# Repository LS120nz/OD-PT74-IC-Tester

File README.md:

# OD-PT74

Pico 74xx Logic IC Tester

OD-PT74 is the first bench instrument in the Otter Designs Test Equipment family.

## PCB Manufacturing

Production-ready PCBs are available from the PCBWay Shared Project.

➡️ https://www.pcbway.com/project/shareproject/OD_PT74_Logic_IC_Tester_728014b9.html

An open-source bench instrument for testing classic 74xx-series logic ICs.

*OD-PT74 Pico 74xx IC Tester installed in the production enclosure.*

---

## Overview

The OD-PT74 Pico 74xx IC Tester is a Raspberry Pi Pico 2 (RP2040) based instrument designed to test common 74xx logic ICs used in retro-computing, electronics repair, education, and hobby projects.

The Rev-C platform combines dedicated hardware, a graphical OLED user interface, and modular MicroPython firmware to provide fast, repeatable testing of common logic devices in a compact desktop instrument.

Current support focuses on standard 14-pin, 16-pin, and 20-pin DIP devices from the 74LS, 74HC, 74HCT and selected compatible logic families.

## 🚀 Quick Start

1. Download or clone this repository.
2. Install **Thonny** from https://thonny.org
3. Install **MicroPython** onto your Raspberry Pi Pico.
4. Copy the following files to the Pico:
   - `main.py`
   - `ssd1306.py`
5. Power up the tester.
6. Verify the POST completes successfully.
7. Start testing ICs!

For detailed installation instructions, see the **Documentation Index** or jump directly to one of the guides below.

---

## Documentation

| Section | Description |
|---------|-------------|
| [📖 Documentation Index](docs/README.md) | Browse all project documentation |
| [🚀 Getting Started](docs/guides/getting-started.md) | First-time setup |
| [🔧 Build Guide](docs/guides/build-guide.md) | Hardware assembly |
| [🔧 Front Panel Wiring Guide](docs/guides/Switch-Wiring-guide.md)
| [💾 Firmware Guide](docs/guides/firmware-guide.md) | Install and update the firmware |
| [▶️ Usage Guide](docs/guides/usage-guide.md) | Operating the tester |
| [🧩 Supported ICs](docs/guides/supported-ics.md) | Supported logic device library |
| [🛠 Troubleshooting Guide](docs/guides/troubleshooting-guide.md) | Diagnose common issues |

---

## Key Features

* Raspberry Pi Pico 2 (RP2040) based design
* Supports standard 14-, 16- and 20-pin DIP packages
* Compatible with common 74LS, 74HC and 74HCT logic families
* Automatic package detection
* Quick, Full and Soak test modes
* Power-On Self Test (POST)
* 128×64 OLED graphical interface
* Rotary encoder driven menu system
* USB serial diagnostics
* Open-source hardware and firmware

---

## Gallery

*Figure 1. Full functional test in progress.*

* 

*Figure 2. OLED displaying a successful PASS result.*

*Figure 3. OLED displaying a FAIL result.*

*Figure 4. USB serial diagnostic output in Thonny.*

## Hardware Summary

| Feature      | Specification                            |
| ------------ | ---------------------------------------- |
| MCU          | Raspberry Pi Pico 2 (RP2040)               |
| Display      | 128 × 64 SSD1306 OLED                    |
| DUT Packages | 14, 16 and 20-pin DIP                    |
| DUT Supply   | 3.3 V / OFF / 5 V                        |
| Interface    | Rotary encoder + push buttons            |
| Firmware     | MicroPython                              |
| License      | MIT (firmware), CERN-OHL-S v2 (hardware) |

---

## Current Release

Hardware PCB Revision: Rev-C
Firmware Version: v1.0.0

This is the first public release of the OD-PT74.

Earlier PCB revisions (Rev-A and Rev-B) were internal development prototypes and were never publicly released.

The project is now focused on:

* expanding the verified IC library
* firmware maintenance and refinement
* documentation improvements
* community contributions

Advanced diagnostic capabilities are planned for the separate Logic IC Diagnostic Analyzer project.

---

## Hardware

Designed for through-hole construction using readily available components with a few SMDs.

Rev-C introduces a production-quality hardware platform featuring:

* Raspberry Pi Pico 2 controller
* 20-pin ZIF socket
* 3.3 V / OFF / 5 V DUT power selection
* Package selection for 14-, 16- and 20-pin devices
* MCP23017 I/O expansion
* SSD1306 OLED display
* Rotary encoder navigation
* TEST and NEXT push buttons
* RGB status LED
* Audible buzzer
* Shared I²C bus architecture
* 5 V power indicator LED
* 3.3 V power indicator LED

GPIO protection is provided through series resistors and clamp diodes to improve robustness during normal operation.

---

## Firmware

The firmware uses a modular architecture that separates hardware drivers, IC definitions, and user interface logic for ease of maintenance and future expansion.

Implemented functionality includes:

* Power-On Self Test (POST)
* OLED diagnostics
* I²C bus diagnostics
* MCP23017 detection
* Package detection
* DUT voltage detection
* Menu-driven user interface
* Serial diagnostic output
* Quick Test mode
* Full Functional Test mode
* Soak testing (50, 500 and Continuous)

---

## Test Modes

| Mode       | Description                                  |
| ---------- | -------------------------------------------- |
| Quick      | Fast functional verification                 |
| Full       | Complete functional testing                  |
| Soak 50    | 50 consecutive test cycles                   |
| Soak 500   | 500 consecutive test cycles                  |
| Continuous | Unlimited endurance testing                  |
| POST       | Automatic hardware self-test during power-up |

During startup the tester automatically verifies:

* OLED communication
* MCP23017 communication
* I²C bus operation
* Package selection
* DUT voltage selection
* TEST button operation

Diagnostic information is displayed on both the OLED and the USB serial console.

---

## Getting Started

1. Assemble the hardware.
2. Install MicroPython on the Raspberry Pi Pico 2.
3. Copy the firmware to the Pico.
4. Power on the tester.
5. Allow the Power-On Self Test to complete.
6. Select the package size.
7. Insert the IC into the ZIF socket.
8. Press **TEST**.

---

## Project Evolution

| Revision | Description                                    |
| -------- | ---------------------------------------------- |
| Rev-C    | First public production release of the OD-PT74 |

Earlier prototype revisions were used during development and are documented in the project history.

---

## Repository Layout

```text
hardware/
firmware/
graphics/
images/
templates/

docs/
├── README.md
├── guides/
├── reference/
├── development/
├── archive/
└── images/

README.md
CHANGELOG.md
CONTRIBUTING.md
LICENSE
```

---

## Contributing

Contributions are welcome, particularly:

* verified IC definitions
* bug reports
* documentation improvements
* hardware testing
* firmware enhancements

When submitting a new IC definition, please include:

* source code
* pin mapping
* tested device family
* hardware validation results
* Quick, Full and Soak test results where applicable

---

## License

Hardware is licensed under the **CERN-OHL-S v2**.

Firmware and documentation are licensed under the **MIT License**.

See the LICENSE file for details.

---

## Acknowledgements

Developed by **Otter Designs**, New Zealand.

If you build an OD-PT74, we'd love to see it! Share your photos, improvements, verified IC definitions, or project ideas by opening an issue or discussion on GitHub.

---

## Project Reference

| Document | Description |
|----------|-------------|
| [📐 Project Overview](docs/reference/project-overview.md) | Project goals and architecture |
| [📘 Hardware Design Guide](docs/reference/hardware-design-guide.md) | Hardware architecture and design |
| [📝 Documentation Style Guide](docs/reference/documentation-style-guide.md) | Documentation standards |

## Development

| Document | Description |
|----------|-------------|
| [📅 Milestones](docs/development/Milestones.md) | Project progress and milestones |

## Project Preservation

Where practical, the OD-PT74 repository includes the original source files used to create the project.

Examples include:

- KiCad PCB source
- FreeCAD enclosure source
- SVG diagrams
- Firmware source code
- Documentation source

This approach helps ensure the project remains buildable, maintainable and adaptable for many years to come.

| [✅ Bring-up Checklist](docs/development/bringup-checklist.md) | Hardware verification checklist |

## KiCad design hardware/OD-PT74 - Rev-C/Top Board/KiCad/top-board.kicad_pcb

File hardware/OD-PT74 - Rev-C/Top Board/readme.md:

# OD-PT74 Rev-C Top Board

This directory contains all design, manufacturing and reference files for the **OD-PT74 Rev-C Top Board**.

## Contents

### BOM

Contains the Bill of Materials in both human-readable Markdown and KiCad-generated CSV formats.

### KiCad

Contains the complete KiCad source project, including the schematic, PCB layout and associated project files.

### Gerbers

Contains the Gerber and drill files generated from the final Rev-C design.

### Images

Contains reference images, including the schematic, PCB layout and 3D board render.

### OD-PT74_Top.zip

A ready-to-upload archive containing all manufacturing files required for PCB fabrication.

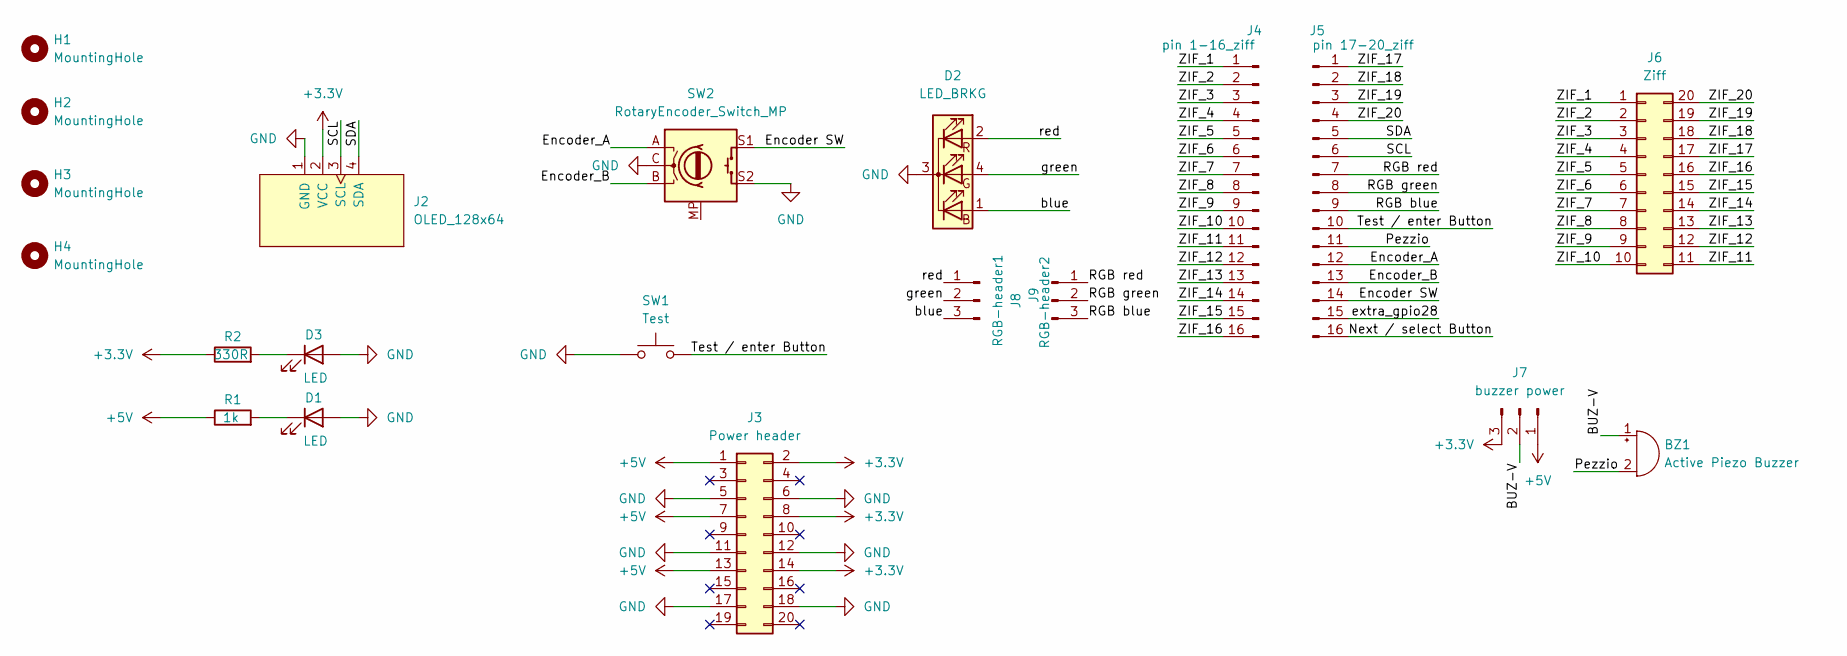
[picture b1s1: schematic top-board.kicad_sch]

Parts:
BZ1: Active Piezo Buzzer; Buzzer_15x7.5RM7.6
D1, D3: LED; LED_D3.0mm
D2: LED_BRKG; LED_D5.0mm-4_RGB_Staggered_Pins
H1, H2, H3, H4: MountingHole; MountingHole_3.2mm_M3
J2: OLED_128x64
J3: Power header; PinHeader_2x10_P2.54mm_Vertical
J4: pin 1-16_ziff; PinHeader_1x16_P2.54mm_Vertical
J5: pin 17-20_ziff; PinHeader_1x16_P2.54mm_Vertical
J6: Ziff; DIP_Socket-20_W4.3mm_W5.08mm_W7.62mm_W10.16mm_W10.9mm_3M_22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
J7: buzzer power; PinHeader_1x03_P2.54mm_Horizontal
J8: RGB-header1; PinHeader_1x03_P2.54mm_Vertical
J9: RGB-header2; PinHeader_1x03_P2.54mm_Vertical
R1: 1k; R_Axial_DIN0207_L6.3mm_D2.5mm_P7.62mm_Horizontal
R2: 330R; R_Axial_DIN0207_L6.3mm_D2.5mm_P7.62mm_Horizontal
SW1: Test; SW_PUSH_6mm
SW2: RotaryEncoder_Switch_MP; RotaryEncoder_Alps_EC11E-Switch_Vertical_H20mm

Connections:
+3.3V: J2.2 (VCC), J3.2, J3.8, J3.14, J7.3, R2.1
+5V: J3.1, J3.7, J3.13, J7.1, R1.1
/BUZ-V: BZ1.1 (+), J7.2
/Encoder SW: J5.14, SW2.S1
/Encoder_A: J5.12, SW2.A
/Encoder_B: J5.13, SW2.B
/Next / select Button: J5.16
/Pezzio: BZ1.2 (-), J5.11
/RGB blue: J5.9, J9.3
/RGB green: J5.8, J9.2
/RGB red: J5.7, J9.1
/SCL: J2.3 (SCL), J5.6
/SDA: J2.4 (SDA), J5.5
/Test / enter Button: J5.10, SW1.2
/ZIF_1: J4.1, J6.1
/ZIF_2: J4.2, J6.2
/ZIF_3: J4.3, J6.3
/ZIF_4: J4.4, J6.4
/ZIF_5: J4.5, J6.5
/ZIF_6: J4.6, J6.6
/ZIF_7: J4.7, J6.7
/ZIF_8: J4.8, J6.8
/ZIF_9: J4.9, J6.9
/ZIF_10: J4.10, J6.10
/ZIF_11: J4.11, J6.11
/ZIF_12: J4.12, J6.12
/ZIF_13: J4.13, J6.13
/ZIF_14: J4.14, J6.14
/ZIF_15: J4.15, J6.15
/ZIF_16: J4.16, J6.16
/ZIF_17: J5.1, J6.17
/ZIF_18: J5.2, J6.18
/ZIF_19: J5.3, J6.19
/ZIF_20: J5.4, J6.20
/blue: D2.1 (BA), J8.3
/extra_gpio28: J5.15
/green: D2.4 (GA), J8.2
/red: D2.2 (RA), J8.1
GND: D1.2 (A), D2.3 (K), D3.2 (A), J2.1 (GND), J3.5, J3.6, J3.11, J3.12, J3.17, J3.18, SW1.1, SW2.C, SW2.S2
unnamed: D1.1 (K), R1.2
unnamed: D3.1 (K), R2.2

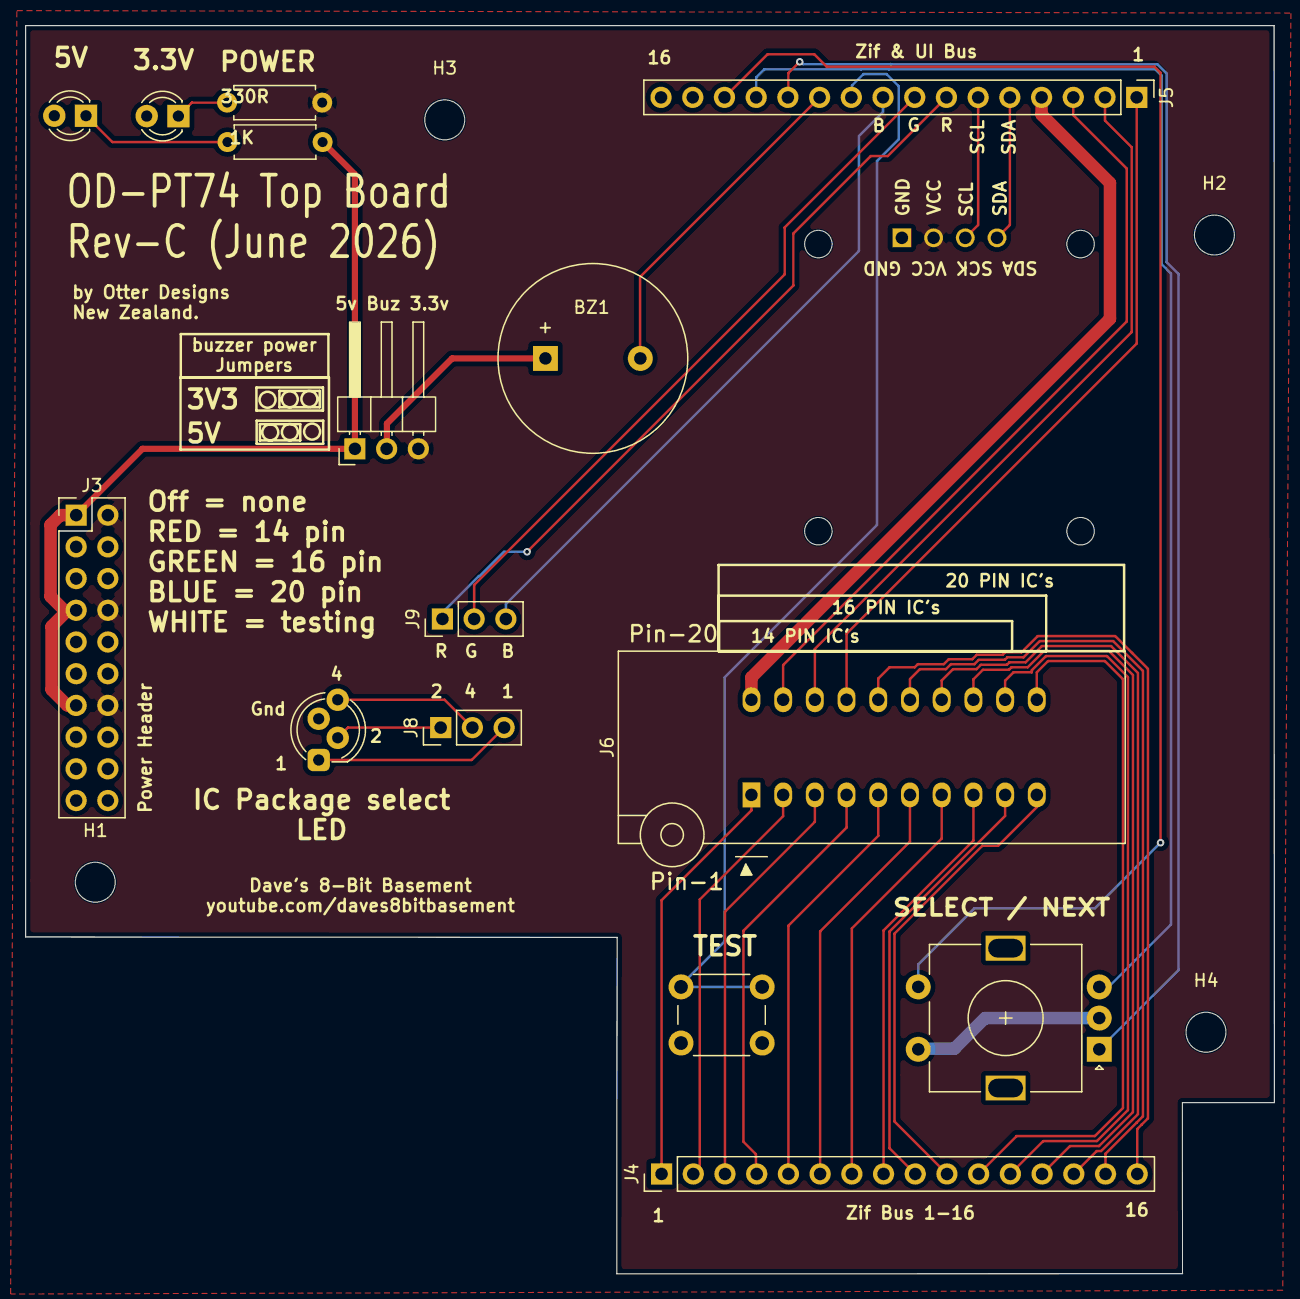
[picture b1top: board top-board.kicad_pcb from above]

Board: 2 copper layers, 100.0 x 100.0 mm, 20 parts (0 on the bottom side), 39 nets.

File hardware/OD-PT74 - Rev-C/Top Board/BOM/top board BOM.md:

# OD-PT74 Rev-C Top Board

*Bill of Materials*
-------------------------

1 × Active Piezo Buzzer (BZ1)

2 × 3 mm Power LEDs (D1, D3)
    - Red
    - Green

1 × RGB LED (D2)

1 × Power Switch, ON/OFF/ON (J1)

1 × 128×64 OLED Display Header (J2)

1 × 2×10 Board Connector (J3)

2 × 1×16 Headers (J4, J5)

1 × 20-pin ZIF Socket

1 × 1 kΩ Resistor (R1)

1 × 330 Ω Resistor (R2)

1 × 6×6 mm Tactile Push Button (SW1)

1 × EC11E Vertical Low-Profile Rotary Encoder (SW2)

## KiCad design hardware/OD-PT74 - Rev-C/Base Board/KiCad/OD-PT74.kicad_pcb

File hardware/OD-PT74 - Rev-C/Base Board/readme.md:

# OD-PT74 Rev-C Base Board

This directory contains all design, manufacturing and reference files for the **OD-PT74 Rev-C Base Board**.

## Contents

### BOM

Contains the Bill of Materials in both human-readable Markdown and KiCad-generated CSV formats.

### KiCad

Contains the complete KiCad source project, including the schematic, PCB layout and associated project files.

### Gerbers

Contains the Gerber and drill files generated from the final Rev-C design.

### Images

Contains reference images, including the schematic, PCB layout and 3D board render.

### OD-PT74_Base.zip
A ready-to-upload archive containing all manufacturing files required for PCB fabrication.

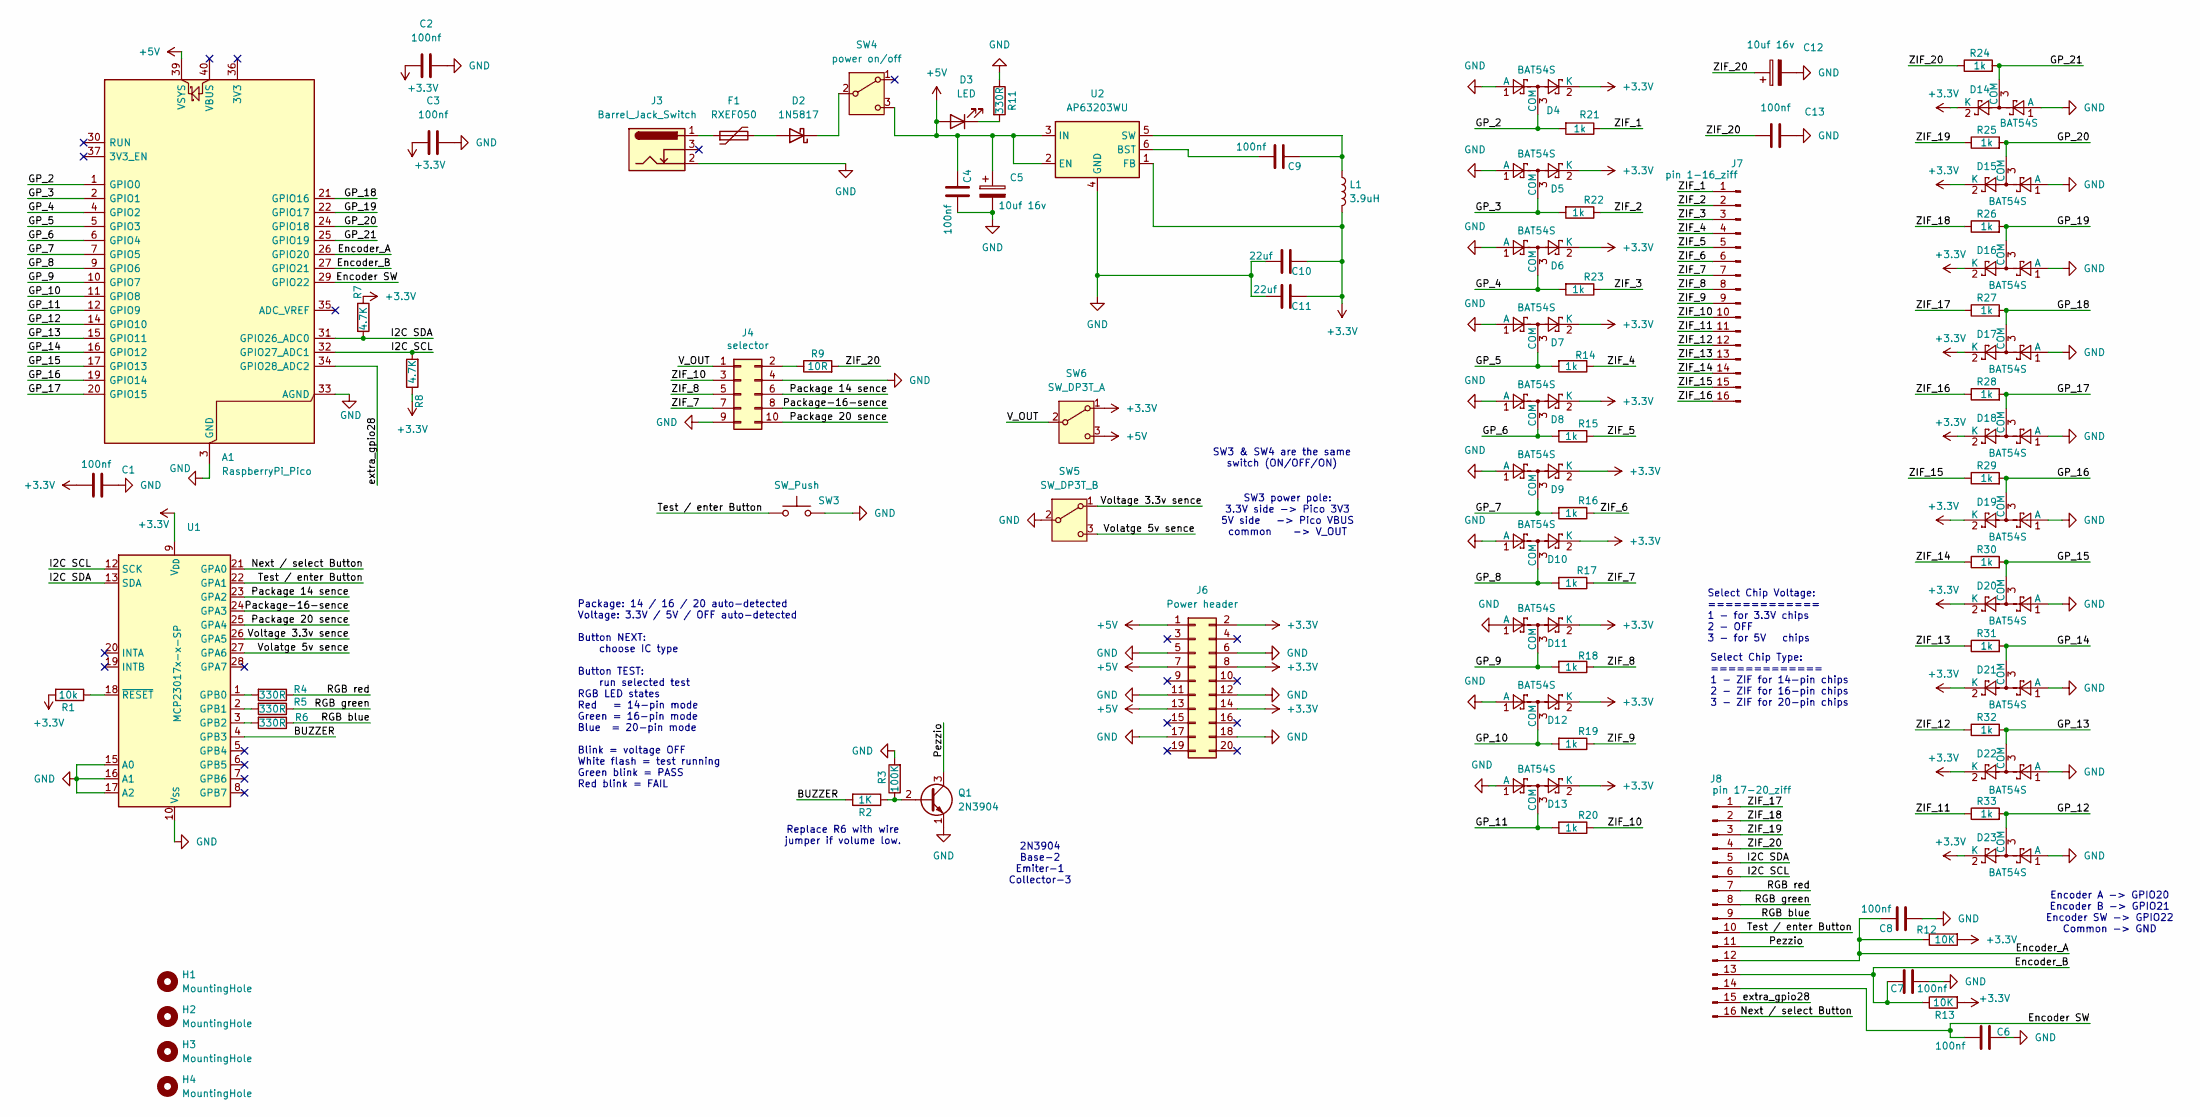
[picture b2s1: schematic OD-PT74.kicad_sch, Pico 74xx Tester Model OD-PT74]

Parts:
A1: RaspberryPi_Pico; RaspberryPi_Pico_Common_THT
C1, C2, C3, C4, C6, C7, C8, C9, C13: 100nf; C_Disc_D6.0mm_W2.5mm_P5.00mm
C5, C12: 10uf 16v; CP_Radial_D8.0mm_P5.00mm
C10, C11: 22uf; C_Disc_D6.0mm_W2.5mm_P5.00mm
D2: 1N5817; D_DO-41_SOD81_P10.16mm_Horizontal
D3: LED; LED_D3.0mm_Clear
D4, D5, D6, D7, D8, D9, D10, D11, D12, D13, D14, D15, D16, D17, D18, D19, D20, D21, D22, D23: BAT54S; SOT-23
F1: RXEF050; Fuse_Littelfuse_395Series
H1, H2, H3, H4: MountingHole; MountingHole_3.2mm_M3
J3: Barrel_Jack_Switch; BarrelJack_Horizontal
J4: selector; PinHeader_2x05_P2.54mm_Vertical
J6: Power header; PinHeader_2x10_P2.54mm_Vertical
J7: pin 1-16_ziff; PinHeader_1x16_P2.54mm_Vertical
J8: pin 17-20_ziff; PinHeader_1x16_P2.54mm_Vertical
L1: 3.9uH; R_Axial_DIN0207_L6.3mm_D2.5mm_P7.62mm_Horizontal
Q1: 2N3904; TO-92L_Wide
R1: 10k; R_Axial_DIN0207_L6.3mm_D2.5mm_P7.62mm_Horizontal
R2: 1K; R_Axial_DIN0207_L6.3mm_D2.5mm_P7.62mm_Horizontal
R3: 100K; R_Axial_DIN0207_L6.3mm_D2.5mm_P7.62mm_Horizontal
R4, R5, R6, R11: 330R; R_Axial_DIN0207_L6.3mm_D2.5mm_P7.62mm_Horizontal
R7, R8: 4.7K; R_Axial_DIN0207_L6.3mm_D2.5mm_P7.62mm_Horizontal
R9: 10R; R_Axial_DIN0207_L6.3mm_D2.5mm_P7.62mm_Horizontal
R12, R13: 10K; R_Axial_DIN0207_L6.3mm_D2.5mm_P7.62mm_Horizontal
R14, R15, R16, R17, R18, R19, R20, R21, R22, R23, R24, R25, R26, R27, R28, R29, R30, R31, R32, R33: 1k; R_Axial_DIN0207_L6.3mm_D2.5mm_P7.62mm_Horizontal
SW3: SW_Push; SW_PUSH_6mm_H7.3mm
SW4: power on/off; PinHeader_1x03_P2.54mm_Vertical
SW5: SW_DP3T_B; PinSocket_1x03_P2.54mm_Vertical
SW6: SW_DP3T_A; PinSocket_1x03_P2.54mm_Vertical
U1: MCP23017x-x-SP; DIP-28_W7.62mm
U2: AP63203WU; TSOT-23-6

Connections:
+3.3V: C1.1, C2.1, C3.1, C10.2, C11.2, D4.2 (K), D5.2 (K), D6.2 (K), D7.2 (K), D8.2 (K), D9.2 (K), D10.2 (K), D11.2 (K), D12.2 (K), D13.2 (K), D14.2 (K), D15.2 (K), D16.2 (K), D17.2 (K), D18.2 (K), D19.2 (K), D20.2 (K), D21.2 (K), D22.2 (K), D23.2 (K), J6.2, J6.8, J6.14, L1.2, R1.2, R7.1, R8.1, R12.2, R13.2, SW6.1 (A), U1.9 (V_{DD}), U2.1 (FB)
+5V: A1.39 (VSYS), C4.2, C5.1, D3.2 (A), J6.1, J6.7, J6.13, SW4.3 (C), SW6.3 (C), U2.2 (EN), U2.3 (IN)
/<NO NET>: J4.8, U1.24 (GPA3)
/BUZZER: R2.2, U1.4 (GPB3)
/Encoder SW: A1.29 (GPIO22), C6.2, J8.14
/Encoder_A: A1.26 (GPIO20), C8.2, J8.12, R12.1
/Encoder_B: A1.27 (GPIO21), C7.2, J8.13, R13.1
/GP_2: A1.1 (GPIO0), D4.3 (COM), R21.2
/GP_3: A1.2 (GPIO1), D5.3 (COM), R22.2
/GP_4: A1.4 (GPIO2), D6.3 (COM), R23.2
/GP_5: A1.5 (GPIO3), D7.3 (COM), R14.2
/GP_6: A1.6 (GPIO4), D8.3 (COM), R15.2
/GP_7: A1.7 (GPIO5), D9.3 (COM), R16.2
/GP_8: A1.9 (GPIO6), D10.3 (COM), R17.2
/GP_9: A1.10 (GPIO7), D11.3 (COM), R18.2
/GP_10: A1.11 (GPIO8), D12.3 (COM), R19.2
/GP_11: A1.12 (GPIO9), D13.3 (COM), R20.2
/GP_12: A1.14 (GPIO10), D23.3 (COM), R33.2
/GP_13: A1.15 (GPIO11), D22.3 (COM), R32.2
/GP_14: A1.16 (GPIO12), D21.3 (COM), R31.2
/GP_15: A1.17 (GPIO13), D20.3 (COM), R30.2
/GP_16: A1.19 (GPIO14), D19.3 (COM), R29.2
/GP_17: A1.20 (GPIO15), D18.3 (COM), R28.2
/GP_18: A1.21 (GPIO16), D17.3 (COM), R27.2
/GP_19: A1.22 (GPIO17), D16.3 (COM), R26.2
/GP_20: A1.24 (GPIO18), D15.3 (COM), R25.2
/GP_21: A1.25 (GPIO19), D14.3 (COM), R24.2
/I2C SCL: A1.32 (GPIO27_ADC1), J8.6, R8.2, U1.12 (SCK)
/I2C SDA: A1.31 (GPIO26_ADC0), J8.5, R7.2, U1.13 (SDA)
/Next / select Button: J8.16, U1.21 (GPA0)
/Package 14 sence: J4.6, U1.23 (GPA2)
/Package 20 sence: J4.10, U1.25 (GPA4)
/Pezzio: J8.11, Q1.3 (C)
/RGB blue: J8.9, R6.1
/RGB green: J8.8, R5.1
/RGB red: J8.7, R4.1
/Test / enter Button: J8.10, SW3.1, U1.22 (GPA1)
/V_OUT: J4.1, SW6.2 (B)
/Volatge 5v sence: SW5.3 (C), U1.27 (GPA6)
/Voltage 3.3v sence: SW5.1 (A), U1.26 (GPA5)
/ZIF_1: J7.1, R21.1
/ZIF_2: J7.2, R22.1
/ZIF_3: J7.3, R23.1
/ZIF_4: J7.4, R14.1
/ZIF_5: J7.5, R15.1
/ZIF_6: J7.6, R16.1
/ZIF_7: J4.7, J7.7, R17.1
/ZIF_8: J4.5, J7.8, R18.1
/ZIF_9: J7.9, R19.1
/ZIF_10: J4.3, J7.10, R20.1
/ZIF_11: J7.11, R33.1
/ZIF_12: J7.12, R32.1
/ZIF_13: J7.13, R31.1
/ZIF_14: J7.14, R30.1
/ZIF_15: J7.15, R29.1
/ZIF_16: J7.16, R28.1
/ZIF_17: J8.1, R27.1
/ZIF_18: J8.2, R26.1
/ZIF_19: J8.3, R25.1
/ZIF_20: C12.1, C13.1, J8.4, R9.2, R24.1
/extra_gpio28: A1.34 (GPIO28_ADC2), J8.15
GND: A1.3 (GND), A1.8 (GND), A1.13 (GND), A1.18 (GND), A1.23 (GND), A1.28 (GND), A1.33 (AGND), A1.38 (GND), C1.2, C2.2, C3.2, C4.1, C5.2, C6.1, C7.1, C8.1, C10.1, C11.1, C12.2, C13.2, D4.1 (A), D5.1 (A), D6.1 (A), D7.1 (A), D8.1 (A), D9.1 (A), D10.1 (A), D11.1 (A), D12.1 (A), D13.1 (A), D14.1 (A), D15.1 (A), D16.1 (A), D17.1 (A), D18.1 (A), D19.1 (A), D20.1 (A), D21.1 (A), D22.1 (A), D23.1 (A), J3.2, J4.4, J4.9, J6.5, J6.6, J6.11, J6.12, J6.17, J6.18, Q1.1 (E), R3.2, R11.1, SW3.2, SW5.2 (B), U1.10 (V_{SS}), U1.15 (A0), U1.16 (A1), U1.17 (A2), U2.4 (GND)
unnamed: D2.2 (A), F1.2
unnamed: D2.1 (K), SW4.2 (B)
unnamed: D3.1 (K), R11.2
unnamed: F1.1, J3.1
unnamed: J4.2, R9.1
unnamed: Q1.2 (B), R2.1, R3.1
unnamed: R4.2, U1.1 (GPB0)
unnamed: R5.2, U1.2 (GPB1)
unnamed: R6.2, U1.3 (GPB2)
unnamed: R1.1, U1.18 (~RESET)
unnamed: C9.1, U2.6 (BST)
unnamed: C9.2, L1.1, U2.5 (SW)

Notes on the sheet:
SW3 power pole: 3.3V side -> Pico 3V3 5V side -> Pico VBUS common -> V_OUT
Select Chip Type: ============= 1 - ZIF for 14-pin chips 2 - ZIF for 16-pin chips 3 - ZIF for 20-pin chips
SW3 & SW4 are the same switch (ON/OFF/ON)
Select Chip Voltage: ============= 1 - for 3.3V chips 2 - OFF 3 - for 5V chips
Replace R6 with wire jumper if volume low.
Package: 14 / 16 / 20 auto-detected Voltage: 3.3V / 5V / OFF auto-detected Button NEXT: choose IC type Button TEST: run selected test RGB LED states Red = 14-pin mode Green = 16-pin mode Blue = 20-pin mode Blink = voltage OFF White flash = test running Green blink = PASS Red blink = FAIL
2N3904 Base-2 Emiter-1 Collector-3
Encoder A -> GPIO20 Encoder B -> GPIO21 Encoder SW -> GPIO22 Common -> GND

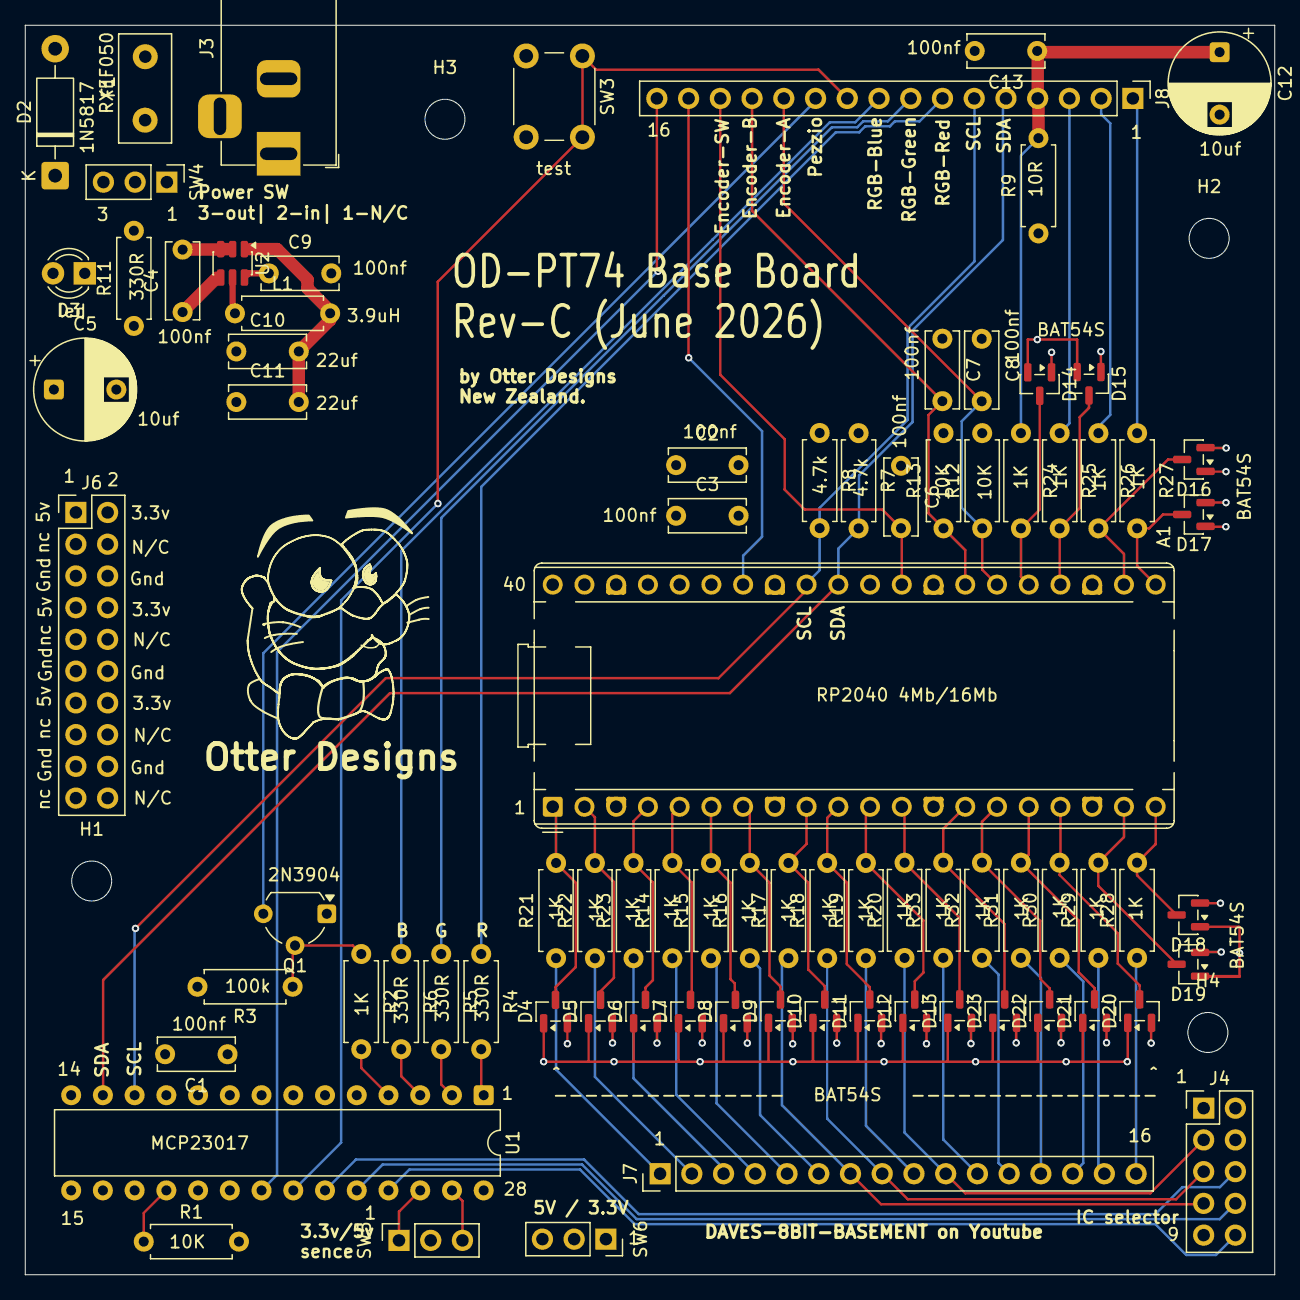
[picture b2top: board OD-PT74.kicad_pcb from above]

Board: 4 copper layers, 100.0 x 100.0 mm, 86 parts (0 on the bottom side), 74 nets.

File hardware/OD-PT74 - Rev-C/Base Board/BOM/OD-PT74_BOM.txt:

Main Board B.O.M Rev-B
------------------
1 x Raspberry-Pi Pico 2040 4Mb+ (A1)
9 x 100nf Disc cap (C1, C2, C3, C4, C6, C7, C8, C9, C13)
2 X 10UF 16V Elec Cap (C5, C12)
2 x 22uf Poly/Disc (C10, C11)
1 x 1N5817 Shockey Diode (D2)
1 x 3mm Led power led (D3)
20 x BAT54S diode (D4 - D23)
1 x RXEF050 resettable fuse (F1)
1 x Barrel Jack (J3)
1 x Selector 3-Pole x 4-Contact (connects to J4)
1 x 2x5 p2.54 Vertical header (J4) (selector header)
1 x 2x10 p2.54 Vertical Socket (J6) (top board Power)
2 x 1x16 p5.54 Vertical Socket (J7,J8) (GPIO headers)
1 x 3.9uH coil (L1)
1 x 2N3904 (Q1)
3 x 10K (R1,R12,R13)
1 x 100K (R3)
4 x 330R (R4,R5,R6,R11)
2 x 4.7K (R7,R8)
1 x 10R (R9)
21 x 1K (R2, R14-R33)
1 x push switch 6x6mm (SW3)
1 x SPST power on/of mains switch (SW7 not in circuit)
1 x DPxTT 3v/5v ic test & scene (for SW5 and SW6) (On/Off/On)
1 x MCP23017 (U1)
1 x AP63203WU (U2)
1 x Dip20 socket
2 x 1x3 2.54 Vertical Header (SW3, SW5, SW6)

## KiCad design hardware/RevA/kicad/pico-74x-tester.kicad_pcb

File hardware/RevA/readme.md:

# Rev A Hardware

## (NOW ARCHIVED FOR HISTORY ONLY!}

This folder contains the Rev A hardware design files for the Pico 74xx IC Tester.

## Contents

### kicad/

Native KiCad project files.

### gerbers/

Manufacturing Gerber files for PCB fabrication.

### bom/

Bill of materials.

### images/

Rendered PCB images and schematics.

---

## Rev A Features

- Raspberry Pi Pico based
- 20-pin ZIF socket
- 14/16/20-pin package support
- 3.3V / OFF / 5V DUT selection
- GPIO protection network
- MCP23017 I/O expander
- RGB status LED
- Passive piezo buzzer
- Optional OLED support

---

## PCB Stackup

| Layer | Purpose |
|---|---|
| Layer 1 | Signals / components |
| Layer 2 | Ground plane |
| Layer 3 | 3.3V / 5V power |
| Layer 4 | Signals |

---

## Current Status

Rev A Finishe and Now Archived for history only !!!

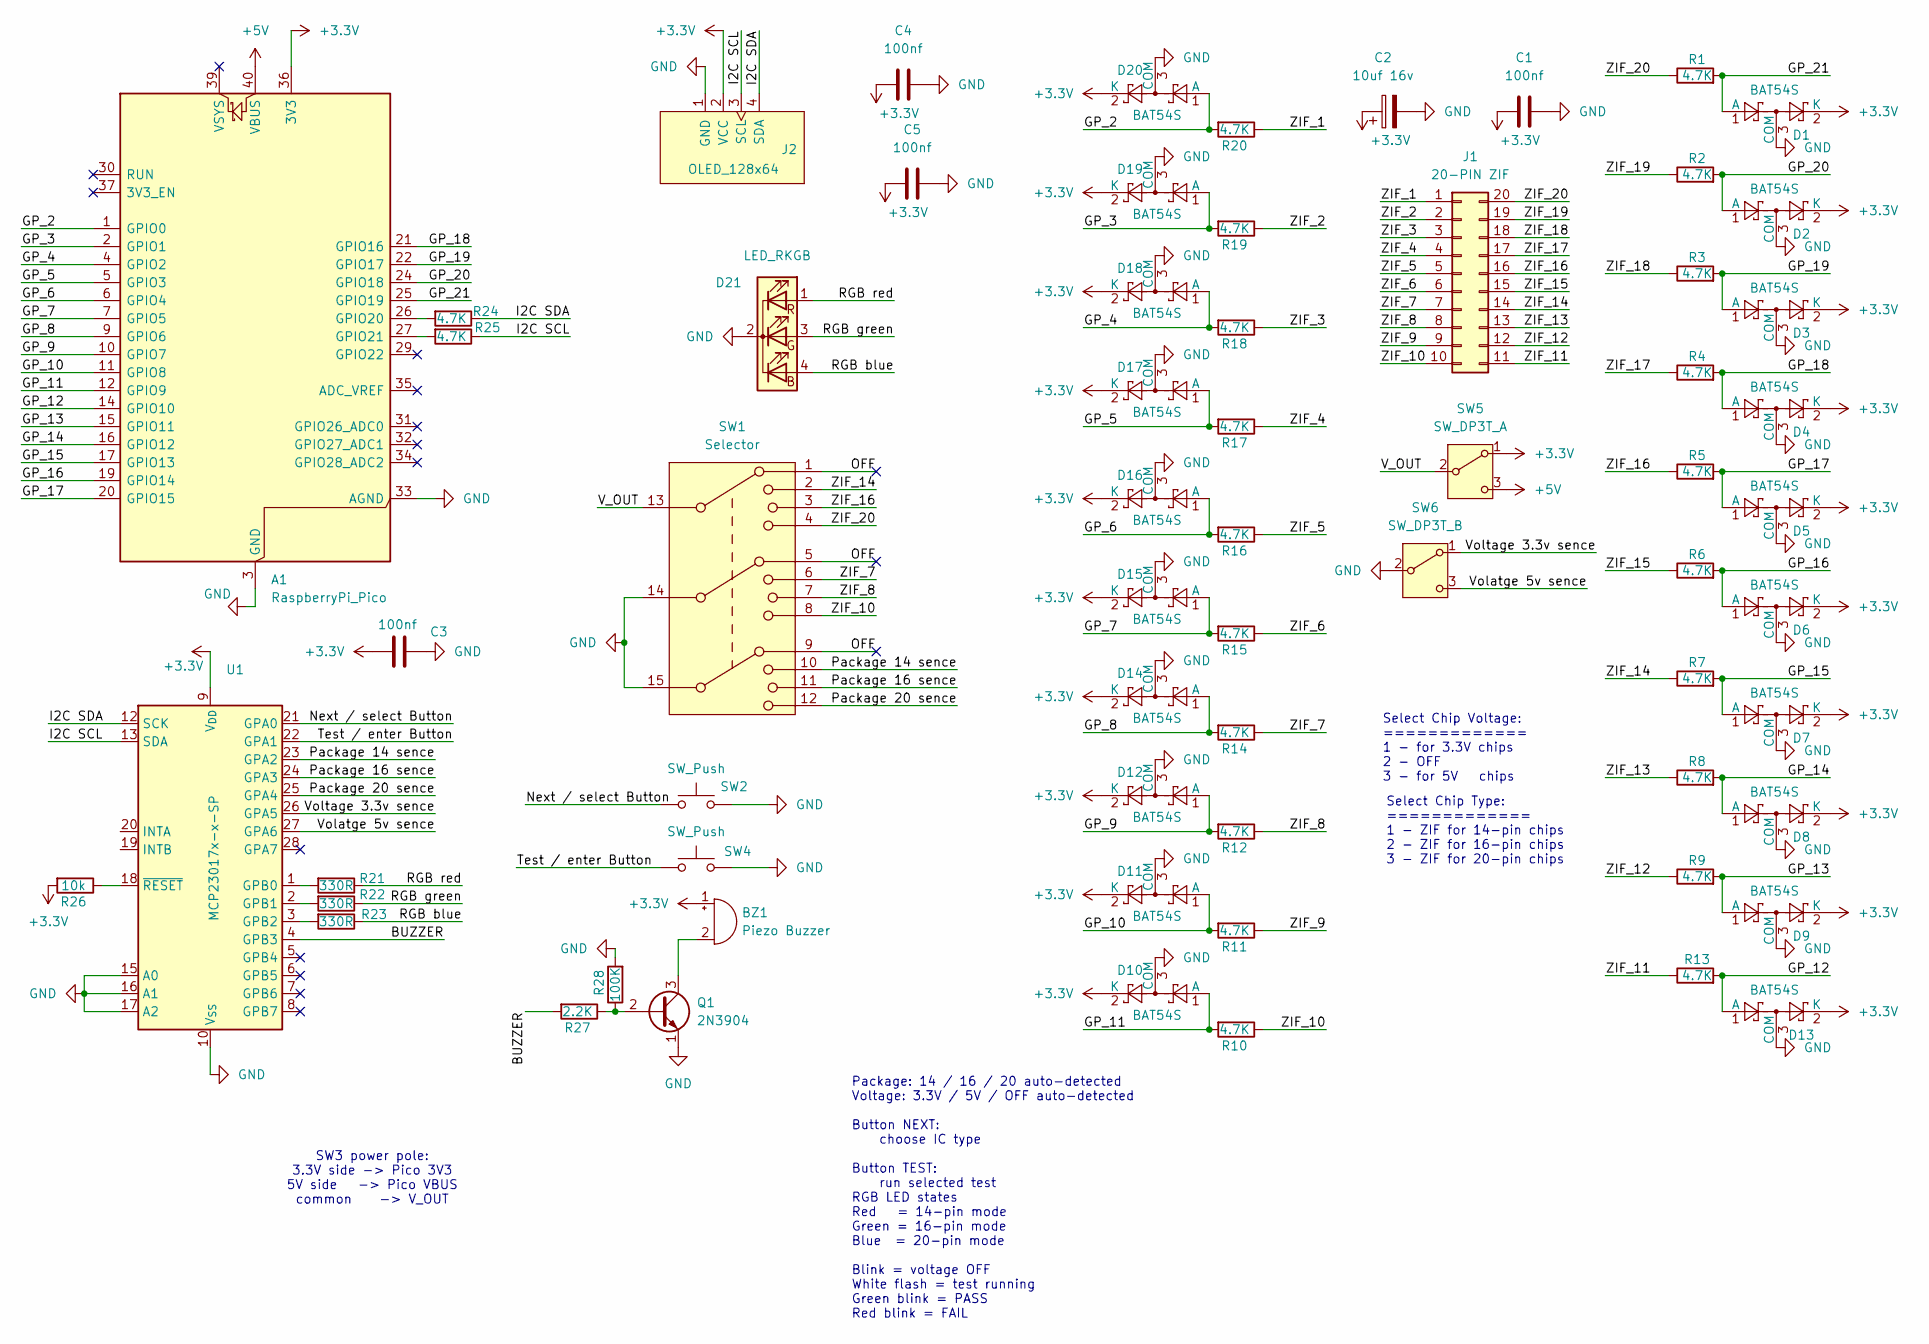
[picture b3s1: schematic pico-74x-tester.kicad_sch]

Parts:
A1: RaspberryPi_Pico; DIP-40_W15.24mm_Socket
BZ1: Piezo Buzzer; Buzzer_15x7.5RM7.6
C1, C3, C4, C5: 100nf; C_Disc_D6.0mm_W2.5mm_P5.00mm
C2: 10uf 16v; CP_Radial_D8.0mm_P5.00mm
D1, D2, D3, D4, D5, D6, D7, D8, D9, D10, D11, D12, D13, D14, D15, D16, D17, D18, D19, D20: BAT54S; SOT-23
D21: LED_RKGB; LED_D5.0mm-4_RGB_Staggered_Pins
J1: 20-PIN ZIF; DIP-20_W7.62mm_Socket
J2: OLED_128x64
Q1: 2N3904; TO-92_Inline
R1, R2, R3, R4, R5, R6, R7, R8, R9, R10, R11, R12, R13, R14, R15, R16, R17, R18, R19, R20, R24, R25: 4.7K; R_Axial_DIN0411_L9.9mm_D3.6mm_P15.24mm_Horizontal
R21, R22, R23: 330R; R_Axial_DIN0411_L9.9mm_D3.6mm_P15.24mm_Horizontal
R26: 10k; R_Axial_DIN0411_L9.9mm_D3.6mm_P15.24mm_Horizontal
R27: 2.2K; R_Axial_DIN0411_L9.9mm_D3.6mm_P15.24mm_Horizontal
R28: 100K; R_Axial_DIN0411_L9.9mm_D3.6mm_P15.24mm_Horizontal
SW1: Selector; PinHeader_2x08_P2.54mm_Vertical
SW2, SW4: SW_Push; SW_PUSH_6mm_H7.3mm
SW5: SW_DP3T_A; PinSocket_1x03_P2.54mm_Vertical
SW6: SW_DP3T_B; PinSocket_1x03_P2.54mm_Vertical
U1: MCP23017x-x-SP; DIP-28_W7.62mm

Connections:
+3.3V: A1.36 (3V3), BZ1.1 (+), C1.1, C2.1, C3.1, C4.1, C5.1, D1.2 (K), D2.2 (K), D3.2 (K), D4.2 (K), D5.2 (K), D6.2 (K), D7.2 (K), D8.2 (K), D9.2 (K), D10.2 (K), D11.2 (K), D12.2 (K), D13.2 (K), D14.2 (K), D15.2 (K), D16.2 (K), D17.2 (K), D18.2 (K), D19.2 (K), D20.2 (K), J2.2 (VCC), R26.2, SW5.1 (A), U1.9 (V_{DD})
+5V: A1.40 (VBUS), SW5.3 (C)
/<NO NET>: SW1.11, U1.24 (GPA3)
/BUZZER: R27.2, U1.4 (GPB3)
/GP_2: A1.1 (GPIO0), D20.1 (A), R20.2
/GP_3: A1.2 (GPIO1), D19.1 (A), R19.2
/GP_4: A1.4 (GPIO2), D18.1 (A), R18.2
/GP_5: A1.5 (GPIO3), D17.1 (A), R17.2
/GP_6: A1.6 (GPIO4), D16.1 (A), R16.2
/GP_7: A1.7 (GPIO5), D15.1 (A), R15.2
/GP_8: A1.9 (GPIO6), D14.1 (A), R14.2
/GP_9: A1.10 (GPIO7), D12.1 (A), R12.2
/GP_10: A1.11 (GPIO8), D11.1 (A), R11.2
/GP_11: A1.12 (GPIO9), D10.1 (A), R10.2
/GP_12: A1.14 (GPIO10), D13.1 (A), R13.2
/GP_13: A1.15 (GPIO11), D9.1 (A), R9.2
/GP_14: A1.16 (GPIO12), D8.1 (A), R8.2
/GP_15: A1.17 (GPIO13), D7.1 (A), R7.2
/GP_16: A1.19 (GPIO14), D6.1 (A), R6.2
/GP_17: A1.20 (GPIO15), D5.1 (A), R5.2
/GP_18: A1.21 (GPIO16), D4.1 (A), R4.2
/GP_19: A1.22 (GPIO17), D3.1 (A), R3.2
/GP_20: A1.24 (GPIO18), D2.1 (A), R2.2
/GP_21: A1.25 (GPIO19), D1.1 (A), R1.2
/I2C SCL: J2.3 (SCL), R25.1, U1.13 (SDA)
/I2C SDA: J2.4 (SDA), R24.1, U1.12 (SCK)
/Next / select Button: SW2.1, U1.21 (GPA0)
/OFF: SW1.1, SW1.5, SW1.9
/Package 14 sence: SW1.10, U1.23 (GPA2)
/Package 20 sence: SW1.12, U1.25 (GPA4)
/RGB blue: D21.4 (BA), R23.1
/RGB green: D21.3 (GA), R22.1
/RGB red: D21.1 (RA), R21.1
/Test / enter Button: SW4.1, U1.22 (GPA1)
/V_OUT: SW1.13, SW5.2 (B)
/Volatge 5v sence: SW6.3 (C), U1.27 (GPA6)
/Voltage 3.3v sence: SW6.1 (A), U1.26 (GPA5)
/ZIF_1: J1.1, R20.1
/ZIF_2: J1.2, R19.1
/ZIF_3: J1.3, R18.1
/ZIF_4: J1.4, R17.1
/ZIF_5: J1.5, R16.1
/ZIF_6: J1.6, R15.1
/ZIF_7: J1.7, R14.1, SW1.6
/ZIF_8: J1.8, R12.1, SW1.7
/ZIF_9: J1.9, R11.1
/ZIF_10: J1.10, R10.1, SW1.8
/ZIF_11: J1.11, R13.1
/ZIF_12: J1.12, R9.1
/ZIF_13: J1.13, R8.1
/ZIF_14: J1.14, R7.1, SW1.2
/ZIF_15: J1.15, R6.1
/ZIF_16: J1.16, R5.1, SW1.3
/ZIF_17: J1.17, R4.1
/ZIF_18: J1.18, R3.1
/ZIF_19: J1.19, R2.1
/ZIF_20: J1.20, R1.1, SW1.4
GND: A1.3 (GND), A1.8 (GND), A1.13 (GND), A1.18 (GND), A1.23 (GND), A1.28 (GND), A1.33 (AGND), A1.38 (GND), C1.2, C2.2, C3.2, C4.2, C5.2, D1.3 (COM), D2.3 (COM), D3.3 (COM), D4.3 (COM), D5.3 (COM), D6.3 (COM), D7.3 (COM), D8.3 (COM), D9.3 (COM), D10.3 (COM), D11.3 (COM), D12.3 (COM), D13.3 (COM), D14.3 (COM), D15.3 (COM), D16.3 (COM), D17.3 (COM), D18.3 (COM), D19.3 (COM), D20.3 (COM), D21.2 (K), J2.1 (GND), Q1.1 (E), R28.2, SW1.14, SW1.15, SW2.2, SW4.2, SW6.2 (B), U1.10 (V_{SS}), U1.15 (A0), U1.16 (A1), U1.17 (A2)
unnamed: A1.26 (GPIO20), R24.2
unnamed: A1.27 (GPIO21), R25.2
unnamed: BZ1.2 (-), Q1.3 (C)
unnamed: Q1.2 (B), R27.1, R28.1
unnamed: R21.2, U1.1 (GPB0)
unnamed: R22.2, U1.2 (GPB1)
unnamed: R23.2, U1.3 (GPB2)
unnamed: R26.1, U1.18 (~RESET)

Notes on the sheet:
SW3 power pole: 3.3V side -> Pico 3V3 5V side -> Pico VBUS common -> V_OUT
Select Chip Type: ============= 1 - ZIF for 14-pin chips 2 - ZIF for 16-pin chips 3 - ZIF for 20-pin chips
Select Chip Voltage: ============= 1 - for 3.3V chips 2 - OFF 3 - for 5V chips
Package: 14 / 16 / 20 auto-detected Voltage: 3.3V / 5V / OFF auto-detected Button NEXT: choose IC type Button TEST: run selected test RGB LED states Red = 14-pin mode Green = 16-pin mode Blue = 20-pin mode Blink = voltage OFF White flash = test running Green blink = PASS Red blink = FAIL

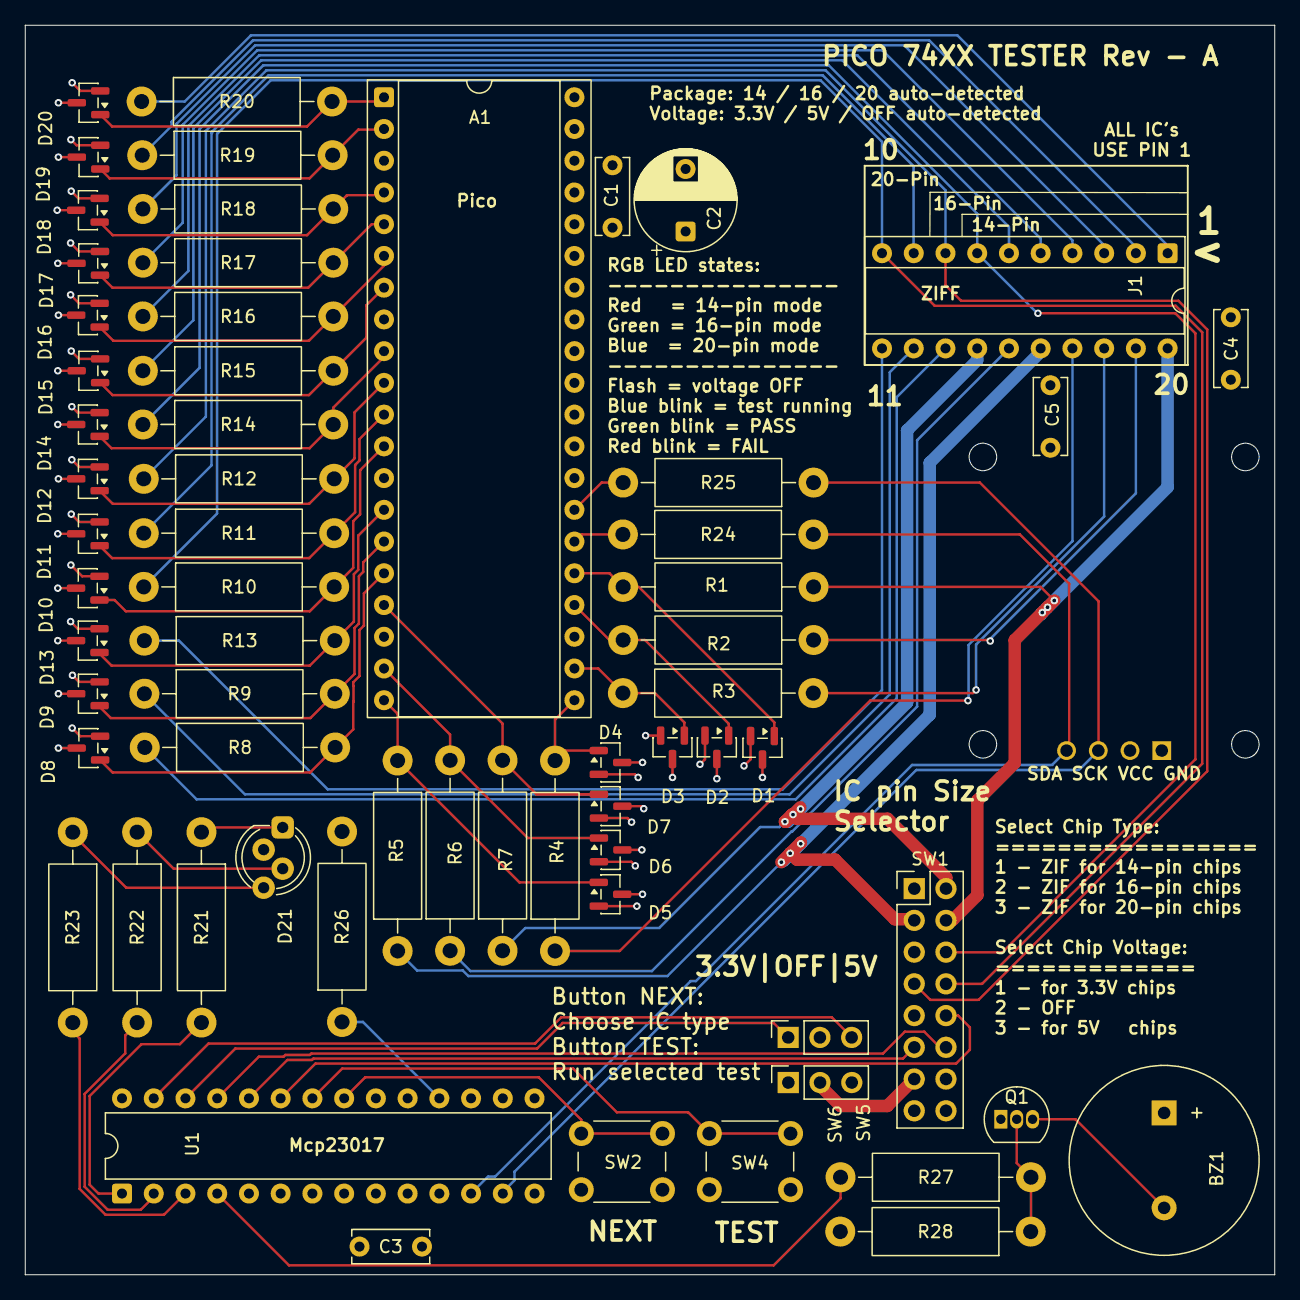
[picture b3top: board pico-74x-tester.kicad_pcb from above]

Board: 4 copper layers, 100.0 x 100.0 mm, 65 parts (0 on the bottom side), 66 nets.

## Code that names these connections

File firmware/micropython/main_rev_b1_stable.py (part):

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last_enc_a = enc_a.value()


# ZIF_1..ZIF_20 -> Pico GPIO0..GPIO19
ZIF_TO_GPIO = {
    1: 0,
    2: 1,
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RGB_R  = 0
RGB_G  = 1
RGB_B  = 2
BUZZER = 3

i2c = SoftI2C(scl=Pin(I2C_SCL), sda=Pin(I2C_SDA), freq=100000)

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

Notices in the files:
README.md:
Hardware: CERN-OHL-S
hardware/OD-PT74 - Rev-C/Base Board/KiCad/OD-PT74.kicad_pcb:
© 2026 David-k Otter
Hardware: CERN-OHL-S v2
